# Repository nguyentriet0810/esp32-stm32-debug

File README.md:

# ESP32 STM32 Debug

Công cụ debug STM32 sử dụng **ESP32-S3 N16R8** làm probe.
Nền tảng phát triển: **ESP-IDF v6.1** trên Windows x64.

## Cấu trúc dự án

```text
esp32-stm32-debug/
├── 01_source/
│   ├── .tooling/
│   │   ├── esp-idf-v6.1/   # Git submodule, ghim đúng commit v6.1
│   │   ├── idf-tools/      # Compiler, CMake, Ninja, GDB, OpenOCD...
│   │   ├── python/         # Python runtime cục bộ
│   │   └── python-env/     # Python environment và các dependency
│   ├── cmake/             # Quy chuẩn build cho mã dự án
│   ├── components/
│   │   ├── probe_board/   # Profile N16R8, kiểm tra bộ nhớ và pin
│   │   ├── probe_bmd/     # Adapter build Black Magic Debug
│   │   ├── probe_debug/   # GDB/TCP, SWD và platform port
│   │   ├── probe_network/ # AP/STA và cấu hình Wi-Fi trong NVS
│   │   ├── probe_wifi_setup/ # Web cấu hình, scan Wi-Fi và Ping gateway router
│   │   ├── probe_state/   # Snapshot trạng thái giữa các task
│   │   ├── probe_console/ # Lệnh chẩn đoán/provision qua UART
│   │   ├── probe_sd/      # microSD SPI/FAT, mount và đọc/ghi có giới hạn
│   │   ├── probe_oled/    # SH1106 I2C và renderer chữ
│   │   ├── probe_encoder/ # A/B, nút và decoder độc lập
│   │   └── probe_local_ui/ # Startup và Settings mẫu, encoder chọn/chỉnh giá trị RAM
│   ├── external/blackmagic/ # Git submodule, backend v2.1.0
│   ├── main/              # Entry point, ghép component và chính sách khởi động
│   ├── tests/             # Bài thử decoder trên PC
│   ├── tooling/           # Dependency lock và constraints được quản lý bằng Git
│   ├── tools/             # Script setup và build
│   ├── CMakeLists.txt
│   ├── partitions.csv
│   ├── sdkconfig.defaults
│   └── tooling.lock.json
├── 02_document/
│   ├── 01_project_overview.md
│   ├── 02_build_and_tooling.md
│   ├── 03_git_workflow.md
│   ├── 04_development_plan.md
│   ├── 05_hardware_and_local_ui.md
│   ├── 06_coding_standard.md
│   ├── 07_misra_deviations.md
│   ├── 08_third_party_notices.md
│   ├── 09_integration_validation.md
│   └── 10_project_logic.md
├── 04_extension_for_vscode/ # Ứng dụng PC: tích hợp probe Wi-Fi vào debugger của project
│   ├── src/                 # Profile probe, gateway RSP, kiểm tra ELF và debug session
│   ├── test/                # Kiểm thử tự động và Extension Host
│   ├── tools/               # Profile phát triển, smoke test và đóng gói VSIX
│   └── README.md            # Hướng dẫn phát triển và sử dụng extension
├── LICENSE
└── README.md
```

## Lập trình firmware ESP32 trong VS Code

Chạy `./open-vscode.ps1` từ thư mục repository để mở
[esp32-probe.code-workspace](esp32-probe.code-workspace) bằng profile VS Code riêng
**ESP32 Probe**. Profile chỉ có ESP-IDF, C/C++ và CMake syntax.
Workspace dùng ESP-IDF v6.1 cục bộ, cấu hình build Debug và console USB native tại COM9.
`Ctrl+Shift+B` để build; `F5` để build, nạp và debug ESP32-S3 qua USB-JTAG.
Task `ESP32: Monitor` mở console; `Ctrl+]` để đóng monitor trước khi nạp/debug.
Hướng dẫn chi tiết nằm trong [Build và bộ công cụ](02_document/02_build_and_tooling.md).

## Phần mềm PC và extension VS Code

[04_extension_for_vscode](04_extension_for_vscode/README.md) chứa phần điều khiển trên PC:
MAGIC v0.2.0 tích hợp probe ESP32 Wi-Fi/SWD vào **Cortex-Debug hoặc bộ debug ST**
đang dùng trong project. Chọn **Use MAGIC Wi-Fi Probe in Project**, rồi dùng cấu hình
MAGIC trong Run and Debug và bấm F5. Build/ELF/toolchain được kế thừa; cấu hình có dây
được giữ lại. Luồng launch F103 có backup đầy đủ và readback verify. Firmware ESP32
được phát triển trong `01_source`.

Mở môi trường phát triển extension bằng profile riêng **MAGIC Probe Extension Dev**:

```powershell
.\04_extension_for_vscode\tools\open-dev.ps1 -InstallDependency
```

Trong workspace extension, nhấn F5 để chạy Extension Development Host.
Hướng dẫn cài VSIX, cấu trúc mã PC và kiểm thử nằm trong README của thư mục này.

## Build nhanh

Nếu bộ công cụ cục bộ đã được chuẩn bị:

```powershell
.\01_source\tools\idf.ps1 --version
.\01_source\tools\idf.ps1 reconfigure build
```

Firmware đầu ra: `01_source/build/stm32_wifi_probe.bin`.
Hướng dẫn cho máy mới: [Build và bộ công cụ](02_document/02_build_and_tooling.md).
Firmware hiện dùng pin cố định theo schematic revision C của PCB REV 1.0:
SWDIO/SWCLK/SWO/nRST = GPIO4/5/6/7, OLED = GPIO8/9, encoder = GPIO15/16/17.
microSD dùng SPI tại GPIO38–42, mount FAT tại `/sdcard`; thiếu thẻ không dừng probe.
Flash N16 đã chia hai slot ESP32 4 MiB, NVS 64 KiB, PHY 8 KiB, otadata 8 KiB,
coredump 256 KiB, hai vùng ảnh STM32 `fw_1`/`fw_2` mỗi vùng 2 MiB và FAT `storage`
3,625 MiB. Nhãn `ota_1`/`ota_2` dùng subtype SDK ota_0/ota_1; app đầu ở `0x20000`.
[Bảng địa chỉ và cách chuyển NVS](02_document/02_build_and_tooling.md#cấu-hình-bộ-nhớ).
Dung lượng đã phân bổ; các luồng OTA, lưu ảnh STM32 và mount FAT nội bộ chưa triển khai.

## Trạng thái

Firmware **0.1.0-dev1** đã từng được build và nạp lên ESP32-S3 N16R8 DevKit ở COM13.
Đã kiểm tra flash 16 MB, PSRAM 8 MB, kết nối Wi-Fi TRIET và GDB/TCP trên phần cứng thật.
Backend Black Magic Debug và SWD port đã tích hợp; thử quét khi chưa có target trả lỗi
có kiểm soát. OLED/encoder đã có driver và menu, hoạt động thiếu OLED không gây dừng probe.

PCB COM9 đã có OLED SH1106, encoder và microSD; firmware báo OLED online, SD mounted.
UI đã có startup, Settings và các màn con SWD/Wi-Fi. Web nhập cấu hình bằng điện thoại
và scan Wi-Fi đã build/nạp, lưu profile và kết nối lại router thật sau reset thành công.
Ping tới hotspot Windows hiện không có phản hồi ICMP; kết nối TCP tới probe vẫn hoạt động.
STM32F103C8 đã đạt scan/attach, breakpoint, step và nạp/verify ví dụ LED PC13 500 ms
qua ARM GDB/Wi-Fi/SWD ở 400 kHz. Timing SWD và đầy đủ thao tác encoder còn cần đo/thử thêm.
MCUViewer acquisition, SWO và USB/CMSIS-DAP ở các mốc sau.
Xem [kết quả kiểm tra và giới hạn](02_document/09_integration_validation.md).

## Kết nối và sử dụng

```powershell
.\01_source\tools\idf.ps1 -p COM13 -b 460800 flash monitor
```

UART console 115200 baud: `help`, `status`, `pins`, `clock 400000`.
Thẻ SD: `sd`, `sd mount`, `sd ls`, `sd read TEST.TXT`,
`sd write TEST.TXT|Hello SD`, `sd unmount`. Tên file dạng 8.3 ở thư mục gốc;
lệnh ghi tạo file mới, không ghi đè. Xem [hướng dẫn microSD](02_document/11_sd_storage.md).
Cấu hình STA bằng `wifi <SSID>|<password>`; firmware lưu vào NVS và tự kết nối sau reset.
Không ghi thông tin đăng nhập vào source hoặc file cấu hình Git. Lệnh `ap` hiển thị
thông tin AP dự phòng trên console khi cần, IP mặc định `192.168.4.1`.

Trên OLED, chọn **Settings → Link → WiFi**, bật **STA setup ON**, nối điện thoại với
AP **MAGIC-PROBE**, mật khẩu **1234567890**, rồi mở **http://192.168.4.1**.
STA setup chỉ bật/tắt cấu hình web, không ngắt STA đang nối router. Khi chưa có STA,
OLED hiện `STA: NONE` và setup luôn ON; sau khi kết nối có thể chủ động chuyển OFF.
Mức **OLED %** được lưu NVS khi nhấn SW chốt và khôi phục sau reset; xem trước/Back không ghi.
50 % chỉ là giá trị dự phòng khi chưa có mức lưu hợp lệ.
Trang cấu hình dùng tiếng Anh: bấm **Scan Wi-Fi**, chọn mạng
trong **Available networks** để điền SSID, nhập mật khẩu router 2,4 GHz rồi bấm **Save and connect**;
cấu hình được lưu NVS, OLED hiện tên STA khi có IP. Ping router nằm trên trang web và
console; màn WiFi OLED có hàng trống dưới tiêu đề, ẩn cả IP/AP/PW khi setup OFF và giữ Back.
Console có `web on`, `web off`, `scan`, `ping` và `net` để cấu hình/chẩn đoán. Xem [hướng dẫn UI/Wi-Fi](02_document/05_hardware_and_local_ui.md).

Dùng IP từ `status` để kết nối ARM GDB:

```text
target extended-remote <probe-ip>:2022
monitor swd_scan
attach 1
```

Chỉ `attach 1` khi scan đã liệt kê target. Chưa có STM32 nối dây thì scan báo lỗi là
kết quả mong đợi. Hướng dẫn đấu nối nằm trong [tài liệu phần cứng](02_document/05_hardware_and_local_ui.md).

Project tiếp tục dùng **Cortex-Debug hoặc STM32CubeIDE for VS Code**;
extension MAGIC tích hợp kết nối tới probe Wi-Fi vào luồng debug đó.
Xem [hướng dẫn và cấu hình attach mẫu](02_document/12_vscode_debug.md).
Mẫu dùng trong project ứng dụng STM32; extension điều khiển PC nằm trong `04_extension_for_vscode`.

## Quản lý phiên bản

Repository: [nguyentriet0810/esp32-stm32-debug](https://github.com/nguyentriet0810/esp32-stm32-debug), chế độ **public**.
Git quản lý firmware, tài liệu, cấu hình mặc định, script và các phiên bản dependency.
ESP-IDF được quản lý bằng submodule; build, cache và binary toolchain được `.gitignore`
loại khỏi commit. Toàn bộ bộ công cụ vẫn nằm cục bộ dưới `01_source/.tooling`.

Xem [Tổng quan dự án](02_document/01_project_overview.md) và
[Quy trình Git](02_document/03_git_workflow.md).

Kiến trúc, vòng đời phiên và luồng debug/nạp firmware theo từng khối:
[Logic hoạt động dự án](02_document/10_project_logic.md).

Kế hoạch các giai đoạn, đầu ra và tiêu chí nghiệm thu:
[Kế hoạch phát triển](02_document/04_development_plan.md).

Pin map và giao diện OLED/encoder:
[Phần cứng và giao diện tại probe](02_document/05_hardware_and_local_ui.md).

## Quy chuẩn mã nguồn và giấy phép

Mã C tự viết dùng C17; adapter cần header Xtensa/FreeRTOS dùng GNU17 với ngoại lệ được ghi rõ.
Component chia theo trách nhiệm, comment API theo Doxygen.
Hướng dẫn mục tiêu là MISRA C:2025; hiện có compiler warnings/GCC analyzer và hồ sơ
ngoại lệ nền tảng, chưa có kết luận tuân thủ MISRA đầy đủ.
Xem [Quy chuẩn viết mã](02_document/06_coding_standard.md) và
[Hồ sơ ngoại lệ](02_document/07_misra_deviations.md).

Giấy phép mã gốc dự án: **GPL-3.0-or-later**, theo lựa chọn giữ hướng Black Magic Debug.
Xem [LICENSE](LICENSE) và [thông báo dependency](02_document/08_third_party_notices.md).

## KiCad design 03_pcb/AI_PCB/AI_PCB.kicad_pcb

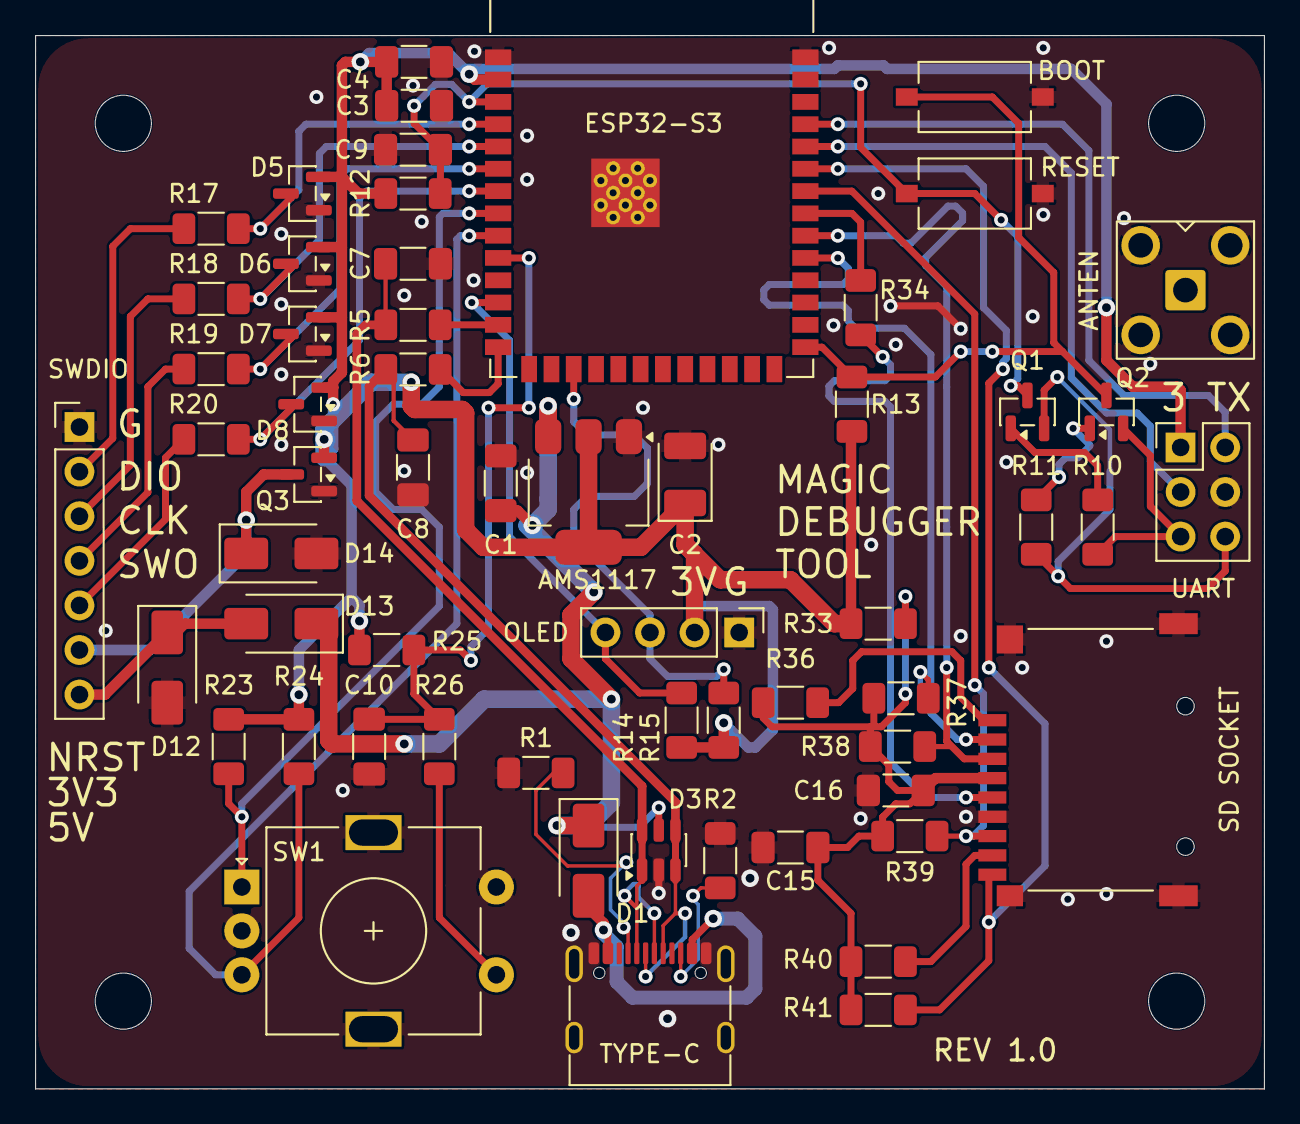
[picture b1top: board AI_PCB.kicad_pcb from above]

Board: 2 copper layers, 70.0 x 60.0 mm, 59 parts (0 on the bottom side), 43 nets.

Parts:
AMS1117: AMS1117-3.3; SOT-223-3_TabPin2
ANTEN: SMA BWSMA-KWE-Z001; SMA_BAT_Wireless_BWSMA-KWE-Z001
BOOT: BOOT; SW_Tactile_SPST_NO_Straight_CK_PTS636Sx25SMTRLFS
C1: 4.7uF; C_1206_3216Metric_Pad1.33x1.80mm_HandSolder
C2: 22uF / 16V Ta; CP_EIA-3528-21_Kemet-B_HandSolder
C3, C15: 10uF; C_1206_3216Metric_Pad1.33x1.80mm_HandSolder
C4, C10, C16: 100nF; C_1206_3216Metric_Pad1.33x1.80mm_HandSolder
C7, C8: 10pF; C_1206_3216Metric_Pad1.33x1.80mm_HandSolder
C9: 1uF; C_1206_3216Metric_Pad1.33x1.80mm_HandSolder
D1, D13: SS34; D_SMA
D3: USBLC6-2SC6; SOT-23-6
D5, D6, D7, D8: BAT54S; SOT-23
D12, D14: SMAJ5.0A; D_SMA
ESP32-S3: ESP32-S3-WROOM-1-N16R8; ESP32-S3-WROOM-1
OLED: SSD1306 I2C; PinHeader_1x04_P2.54mm_Vertical
Q1, Q2: MMBT3904; SOT-23
Q3: AO3401A; SOT-23
R1, R2: 5.1k 1%; R_1206_3216Metric_Pad1.30x1.75mm_HandSolder
R5, R6, R34: 22R; R_1206_3216Metric_Pad1.30x1.75mm_HandSolder
R10, R11, R12, R13, R23, R24, R25, R36, R37, R38, R39, R40, R41: 10k; R_1206_3216Metric_Pad1.30x1.75mm_HandSolder
R14, R15: 4.7k; R_1206_3216Metric_Pad1.30x1.75mm_HandSolder
R17, R18, R19, R20: 330R; R_1206_3216Metric_Pad1.30x1.75mm_HandSolder
R26: 1k; R_1206_3216Metric_Pad1.30x1.75mm_HandSolder
R33: 0R; R_1206_3216Metric_Pad1.30x1.75mm_HandSolder
RESET: RESET; SW_Tactile_SPST_NO_Straight_CK_PTS636Sx25SMTRLFS
SD SOCKET: JXTCONN TF-01A; JXTCONN_TF-01A
SW1: EC11-style encoder; RotaryEncoder_Alps_EC11E-Switch_Vertical_H20mm
SWDIO: PinHeader_1x07_P2.54mm_Vertical
TYPE-C: USB-C Native; USB_C_Receptacle_G-Switch_GT-USB-7010ASV
UART: UART_3V3_TX_RX_GND_DTR_RTS; PinHeader_2x03_P2.54mm_Vertical

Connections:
/+3V3: AMS1117.2 (VO), C2.1, C3.1, C4.1, D5.2 (K), D6.2 (K), D7.2 (K), D8.2 (K), ESP32-S3.2 (3V3), OLED.2, Q3.2 (S), R12.1, R13.1, R14.1, R15.1, R23.1, R24.1, R25.1, R33.1, UART.1
/ENC_A: ESP32-S3.8 (IO15), R23.2, SW1.A
/ENC_B: ESP32-S3.9 (IO16), R24.2, SW1.B
/ENC_CONTACT: R26.1, SW1.S1
/ENC_SW: C10.1, ESP32-S3.10 (IO17), R25.2, R26.2
/ESP_BOOT: BOOT.1, ESP32-S3.27 (IO0), Q2.3 (C), R13.2
/ESP_EN: C9.1, ESP32-S3.3 (EN), Q1.3 (C), R12.2, RESET.1
/ESP_USB_N: ESP32-S3.13 (USB_D-), R5.2
/ESP_USB_P: ESP32-S3.14 (USB_D+), R6.2
/EXT_NRST: R20.1, SWDIO.5
/EXT_SWCLK: R18.1, SWDIO.3
/EXT_SWDIO: R17.1, SWDIO.2
/EXT_SWO: R19.1, SWDIO.4
/GND: AMS1117.1 (GND), ANTEN.2 (Ext_2), BOOT.2, C1.2, C2.2, C3.2, C4.2, C7.2, C8.2, C9.2, C10.2, C15.2, C16.2, D3.2 (GND), D5.1 (A), D6.1 (A), D7.1 (A), D8.1 (A), D12.2 (A), D14.2 (A), ESP32-S3.1 (GND), ESP32-S3.40 (GND), ESP32-S3.41 (GND), OLED.1, Q3.1 (G), R1.2, R2.2, RESET.2, SD SOCKET.6 (VSS), SD SOCKET.SH (SHIELD), SW1.C, SW1.MP, SW1.S2, SWDIO.1, TYPE-C.A1 (GND), TYPE-C.A12 (GND), TYPE-C.B1 (GND), TYPE-C.B12 (GND), TYPE-C.SH (SHIELD), UART.4
/J1_CC1: R1.1, TYPE-C.A5 (CC1)
/J1_CC2: R2.1, TYPE-C.B5 (CC2)
/J4_3V3_IN: D14.1 (K), Q3.3 (D), SWDIO.6
/J4_5V_IN: D12.1 (K), D13.2 (A), SWDIO.7
/OLED_SCL: ESP32-S3.17 (IO9), OLED.3, R15.2
/OLED_SDA: ESP32-S3.12 (IO8), OLED.4, R14.2
/SD_3V3: C15.1, C16.1, R33.2, R36.1, R37.1, R38.1, R39.1, R40.1, R41.1, SD SOCKET.4 (VDD)
/SD_CLK: R34.2, SD SOCKET.5 (CLK)
/SD_CS_N: ESP32-S3.31 (IO38), R37.2, SD SOCKET.2 (DAT3/CD)
/SD_DAT1: R40.2, SD SOCKET.8 (DAT1)
/SD_DAT2: R36.2, SD SOCKET.1 (DAT2)
/SD_DETECT_N: ESP32-S3.35 (IO42), R41.2, SD SOCKET.9 (DET)
/SD_MISO: ESP32-S3.34 (IO41), R39.2, SD SOCKET.7 (DAT0)
/SD_MOSI: ESP32-S3.32 (IO39), R38.2, SD SOCKET.3 (CMD)
/SD_SCK: ESP32-S3.33 (IO40), R34.1
/SWCLK: D6.3 (COM), ESP32-S3.5 (IO5), R18.2
/SWDIO: D5.3 (COM), ESP32-S3.4 (IO4), R17.2
/SWO: D7.3 (COM), ESP32-S3.6 (IO6), R19.2
/TARGET_NRST: D8.3 (COM), ESP32-S3.7 (IO7), R20.2
/UART_DTR_N: Q2.2 (E), R10.1, UART.5
/UART_RTS_N: Q1.2 (E), R11.1, UART.6
/UART_RX_HDR: ESP32-S3.36 (RXD0), UART.3
/UART_TX_HDR: ESP32-S3.37 (TXD0), UART.2
/USB_N_N: C7.1, D3.1 (I/O1), D3.6 (I/O1), R5.1, TYPE-C.A7 (D-), TYPE-C.B7 (D-)
/USB_N_P: C8.1, D3.3 (I/O2), D3.4 (I/O2), R6.1, TYPE-C.A6 (D+), TYPE-C.B6 (D+)
/VBUS_NATIVE: D1.2 (A), TYPE-C.A4 (VBUS), TYPE-C.A9 (VBUS), TYPE-C.B4 (VBUS), TYPE-C.B9 (VBUS)
/VBUS_OR: AMS1117.3 (VI), C1.1, D1.1 (K), D3.5 (VBUS), D13.1 (K)
unnamed: Q1.1 (B), R10.2
unnamed: Q2.1 (B), R11.2

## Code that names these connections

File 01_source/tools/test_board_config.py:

#!/usr/bin/env python3
# SPDX-FileCopyrightText: 2026 Nguyen Hoang Minh Triet
# SPDX-License-Identifier: GPL-3.0-or-later
"""Check PCB GPIOs and firmware defaults against an exported KiCad XML netlist.

This is an offline configuration check, not a runtime hardware test. Export the
current schematic with kicad-cli before running; old netlists can hide changes.
"""

import argparse
from pathlib import Path
import re
import sys
import xml.etree.ElementTree as ET


SIGNALS = (
    ("PROBE_SWDIO_GPIO", "SWDIO", 4),
    ("PROBE_SWCLK_GPIO", "SWCLK", 5),
    ("PROBE_SWO_GPIO", "SWO", 6),
    ("PROBE_NRST_GPIO", "TARGET_NRST", 7),
    ("PROBE_OLED_SDA_GPIO", "OLED_SDA", 8),
    ("PROBE_OLED_SCL_GPIO", "OLED_SCL", 9),
    ("PROBE_ENCODER_A_GPIO", "ENC_A", 15),
    ("PROBE_ENCODER_B_GPIO", "ENC_B", 16),
    ("PROBE_ENCODER_SW_GPIO", "ENC_SW", 17),
    ("PROBE_SD_CS_GPIO", "SD_CS_N", 38),
    ("PROBE_SD_MOSI_GPIO", "SD_MOSI", 39),
    ("PROBE_SD_SCK_GPIO", "SD_SCK", 40),
    ("PROBE_SD_MISO_GPIO", "SD_MISO", 41),
    ("PROBE_SD_DETECT_GPIO", "SD_DETECT_N", 42),
)
OPTIONAL_PERIPHERALS = ("PROBE_OLED_ENABLE", "PROBE_ENCODER_ENABLE", "PROBE_SD_ENABLE")


def read_kconfig_defaults(path):
    """Return first unconditional scalar defaults indexed by Kconfig symbol.

    Args:
        path: UTF-8 board Kconfig path.
    Returns:
        A new symbol-to-text dictionary; the source file is not modified.
    """
    result = {}
    symbol = None
    for line in path.read_text(encoding="utf-8").splitlines():
        match = re.fullmatch(r"config\s+(\w+)\s*", line)
        if match:
            symbol = match[1]
        elif symbol:
            match = re.fullmatch(r"\s+default\s+(\S+)\s*", line)
            if match:
                result.setdefault(symbol, match[1])
    return result


def read_sdkconfig(path):
    """Parse SDK configuration values, including disabled-bool comment syntax.

    Args:
        path: UTF-8 defaults or generated sdkconfig file.
    Returns:
        Symbol values as strings, with disabled bools represented by "n".
    """
    result = {}
    for line in path.read_text(encoding="utf-8").splitlines():
        match = re.fullmatch(r"CONFIG_(\w+)=(.*)", line)
        if match:
            result[match[1]] = match[2]
        else:
            match = re.fullmatch(r"# CONFIG_(\w+) is not set", line)
            if match:
                result[match[1]] = "n"
    return result


def check_netlist(path, errors):
    """Append schematic pin and connector mismatches to the caller-owned errors list.

    Args:
        path: Freshly exported KiCad XML netlist.
        errors: Mutable diagnostic list updated in place.
    Raises:
        OSError: The netlist cannot be read.
        ET.ParseError: The input is not valid XML.
    """
    tree = ET.parse(path)
    nets = {}
    pins = {}
    for net in tree.findall("./nets/net"):
        name = net.get("name", "").lstrip("/")
        nets.setdefault(name, []).append(net)
        for node in net.findall("node"):
            key = (node.get("ref"), node.get("pin"))
            pins.setdefault(key, []).append(name)

    for _, signal, expected_gpio in SIGNALS:
        nodes = [
            node
            for net in nets.get(signal, [])
            for node in net.findall("node")
            if node.get("ref") == "U1"
        ]
        actual = [node.get("pinfunction", "") for node in nodes]
        if len(nodes) != 1 or re.fullmatch(
            rf"IO{expected_gpio}(?:_\d+)?", actual[0] if actual else ""
        ) is None:
            errors.append(
                f"{path}: /{signal} must connect to U1 GPIO{expected_gpio}; "
                f"found U1 pin functions {actual or 'none'}"
            )

    def expect_pin(reference, pin, expected_net):
        """Append a diagnostic unless one connector pin has exactly the expected net."""
        actual = pins.get((reference, pin), [])
        if actual != [expected_net]:
            errors.append(
                f"{path}: {reference}.{pin} must be on /{expected_net}; "
                f"found {actual or 'no connection'}"
            )

    for pin, net in (("1", "GND"), ("2", "+3V3"), ("3", "OLED_SCL"), ("4", "OLED_SDA")):
        expect_pin("J3", pin, net)
    expect_pin("J4", "1", "GND")
    for header_pin, resistor, mcu_net, external_net in (
        ("2", "R17", "SWDIO", "EXT_SWDIO"),
        ("3", "R18", "SWCLK", "EXT_SWCLK"),
        ("4", "R19", "SWO", "EXT_SWO"),
        ("5", "R20", "TARGET_NRST", "EXT_NRST"),
    ):
        expect_pin("J4", header_pin, external_net)
        expect_pin(resistor, "1", external_net)
        expect_pin(resistor, "2", mcu_net)
    for pin, net in (
        ("2", "SD_CS_N"), ("3", "SD_MOSI"), ("4", "SD_3V3"),
        ("5", "SD_CLK"), ("6", "GND"), ("7", "SD_MISO"),
        ("9", "SD_DETECT_N"), ("SH", "GND"),
    ):
        expect_pin("J5", pin, net)
    expect_pin("R34", "1", "SD_SCK")
    expect_pin("R34", "2", "SD_CLK")
    expect_pin("R41", "1", "SD_3V3")
    expect_pin("R41", "2", "SD_DETECT_N")


def check_config(values, label, errors, generated=False):
    """Append PCB configuration mismatches without altering the supplied values.

    Args:
        values: Symbol-to-text configuration dictionary.
        label: Source label included in diagnostics.
        errors: Caller-owned list to which mismatches are appended.
        generated: Permit explicit enable/disable choices for optional peripherals.
    """
    expected = {symbol: str(gpio) for symbol, _, gpio in SIGNALS}
    if not generated:
        expected.update({symbol: "y" for symbol in OPTIONAL_PERIPHERALS})
    expected["PROBE_BOARD_PCB_REV_C"] = "y"
    for symbol, value in expected.items():
        actual = values.get(symbol)
        if actual != value:
            errors.append(
                f"{label}: CONFIG_{symbol} must be {value}; "
                f"found {actual if actual is not None else 'missing'}"
            )
    if generated:
        for symbol in OPTIONAL_PERIPHERALS:
            actual = values.get(symbol)
            if actual not in ("y", "n"):
                errors.append(
                    f"{label}: CONFIG_{symbol} must be y or n; "
                    f"found {actual if actual is not None else 'missing'}"
                )


def main():
    """Compare schematic, defaults and optional generated configuration from CLI arguments.

    Returns:
        Zero on agreement, or one after printing accumulated diagnostics.
    """
    parser = argparse.ArgumentParser(description=__doc__)
    parser.add_argument("--netlist", type=Path, required=True, help="Fresh KiCad XML netlist")
    parser.add_argument("--sdkconfig", type=Path, help="Also check the generated build configuration")
    args = parser.parse_args()
    source = Path(__file__).resolve().parents[1]
    kconfig_path = source / "components" / "probe_board" / "Kconfig"
    defaults_path = source / "sdkconfig.defaults"
    errors = []
    try:
        check_netlist(args.netlist, errors)
        kconfig = read_kconfig_defaults(kconfig_path)
        check_config(kconfig, kconfig_path, errors)
        defaults = {**kconfig, **read_sdkconfig(defaults_path)}
        check_config(defaults, f"{defaults_path} (with Kconfig defaults)", errors)
        if args.sdkconfig:
            check_config(read_sdkconfig(args.sdkconfig), args.sdkconfig, errors, generated=True)
    except (OSError, ET.ParseError) as error:
        errors.append(str(error))
    if errors:
        for error in errors:
            print(f"FAIL: {error}", file=sys.stderr)
        return 1
    print("PASS: 14 schematic GPIOs, OLED/debug/SD connectors and firmware PCB defaults agree")
    if args.sdkconfig:
        print(f"PASS: generated configuration {args.sdkconfig} matches the PCB")
    print("Offline configuration check only; runtime hardware is not tested.")
    return 0


if __name__ == "__main__":
    sys.exit(main())
